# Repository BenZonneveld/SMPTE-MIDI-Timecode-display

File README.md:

# SMPTE-MIDI-Timecode-display
Components needed for the hardware:
2x  Adafruit 1.2" 4-Digit 7-Segment Display w/I2C Backpack - (Red or any available color you like)
1x  Arduino Micro (ATmega 32u4 based microcontroller with USB)
4x  5 pin male header
some cabling to connect the displays to the Arduino i2c, see schematic.

Needed for SMPTE reading:
the 6.3 mm jack, transistor etc.

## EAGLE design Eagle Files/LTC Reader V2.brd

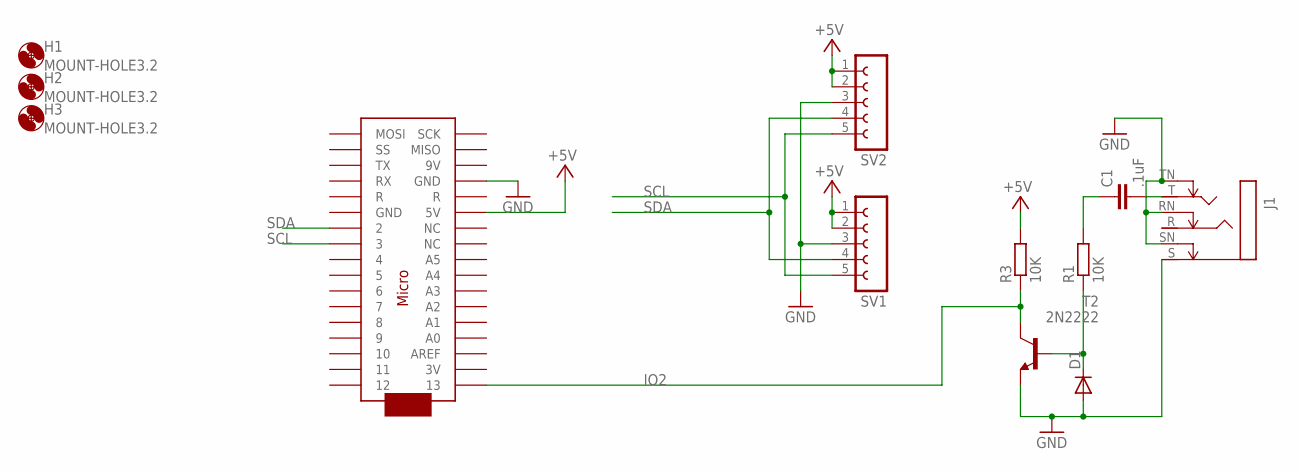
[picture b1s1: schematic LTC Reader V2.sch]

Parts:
C1: .1uF; C5B2.5
D1: 1N4148DO35-7; DO35-7
H1, H2, H3: MOUNT-HOLE3.2; 3,2
J1: STEREOSWS; NMJ6HC-S
R1, R3: 10K; 0207/10
SV1, SV2: FE05-1
T2: 2N2222; TO92-EBC-OVAL
U$1: ARDUINOMICRO

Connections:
+5V: R3.2, SV1.1, SV1.2, SV2.1, SV2.2, U$1.P$23 (5V)
GND: D1.A, J1.RN, J1.S, J1.SN, J1.TN, SV1.3, SV2.3, T2.E, U$1.P$12 (GND)
IO2: R3.1, T2.C, U$1.P$34 (13)
unnamed: C1.1, R1.2
unnamed: D1.C, R1.1, T2.B
unnamed: C1.2, J1.T
SCL: SV1.5, SV2.5, U$1.P$10 (3)
SDA: SV1.4, SV2.4, U$1.P$11 (2)

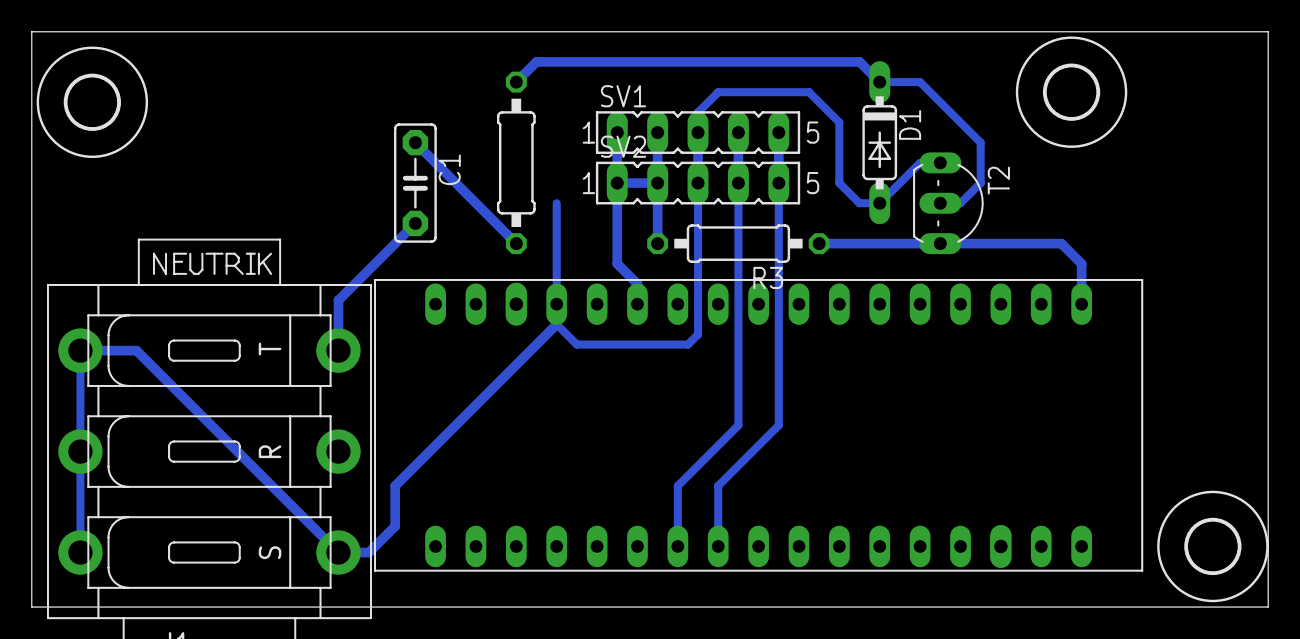
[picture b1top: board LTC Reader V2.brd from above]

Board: 2 copper layers, 77.8 x 36.2 mm, 12 parts (0 on the bottom side), 8 nets.

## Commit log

2021-06-17 The source code for my SMPTE / MIDI Timecode display using an Arduino Micro or any other ATmega32u4 basic microcontroller
2021-06-17 Added the eagle files for the project
2021-06-17 Added a PNG of the schematic
